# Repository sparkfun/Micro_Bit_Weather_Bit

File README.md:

SparkFun weather:bit - micro:bit Carrier Board (Qwiic)
========================================

[*SparkFun weather:bit (DEV-15837)*](https://www.sparkfun.com/products/15837)

The SparkFun weather:bit is a fully loaded “carrier” board for the micro:bit that, when combined with the micro:bit, provides you with a fully functional weather station. With the weather:bit you will have access to barometric pressure, relative humidity and temperature readings. There are also connections on this carrier board to optional sensors such as wind speed, direction, rain gauge and soil readings! The micro:bit has a lot of features and a lot of potential for weather data collection.

Repository Contents
-------------------

* **/Firmware** -  Example code used in the micro:climate Kit Experiment Guide. While they are compiled HEX codes, you can modify the example code once they are imported into MakeCode editor.
* **/Hardware** - Eagle design files (.brd, .sch)
* **/Production** - Production panel files (.brd)

Documentation
--------------
* **[Library](https://github.com/sparkfun/pxt-weather-bit)** - PXT weather:bit firmware
* **[micro:Climate Kit Experiment Guide](https://learn.sparkfun.com/tutorials/microclimate-kit-experiment-guide)** - Experiment guide using the weather:bit carrier board.
* **[Wireless Remote Weather Station with micro:bit](https://learn.sparkfun.com/tutorials/wireless-remote-weather-station-with-microbit/)** - Additional experiments for transmitting weather data wirelessly.

License Information
-------------------

This product is _**open source**_! 

Please review the LICENSE.md file for license information. 

If you have any questions or concerns on licensing, please contact technical support on our [SparkFun forums](https://forum.sparkfun.com/viewforum.php?f=152).

Distributed as-is; no warranty is given.

- Your friends at SparkFun.

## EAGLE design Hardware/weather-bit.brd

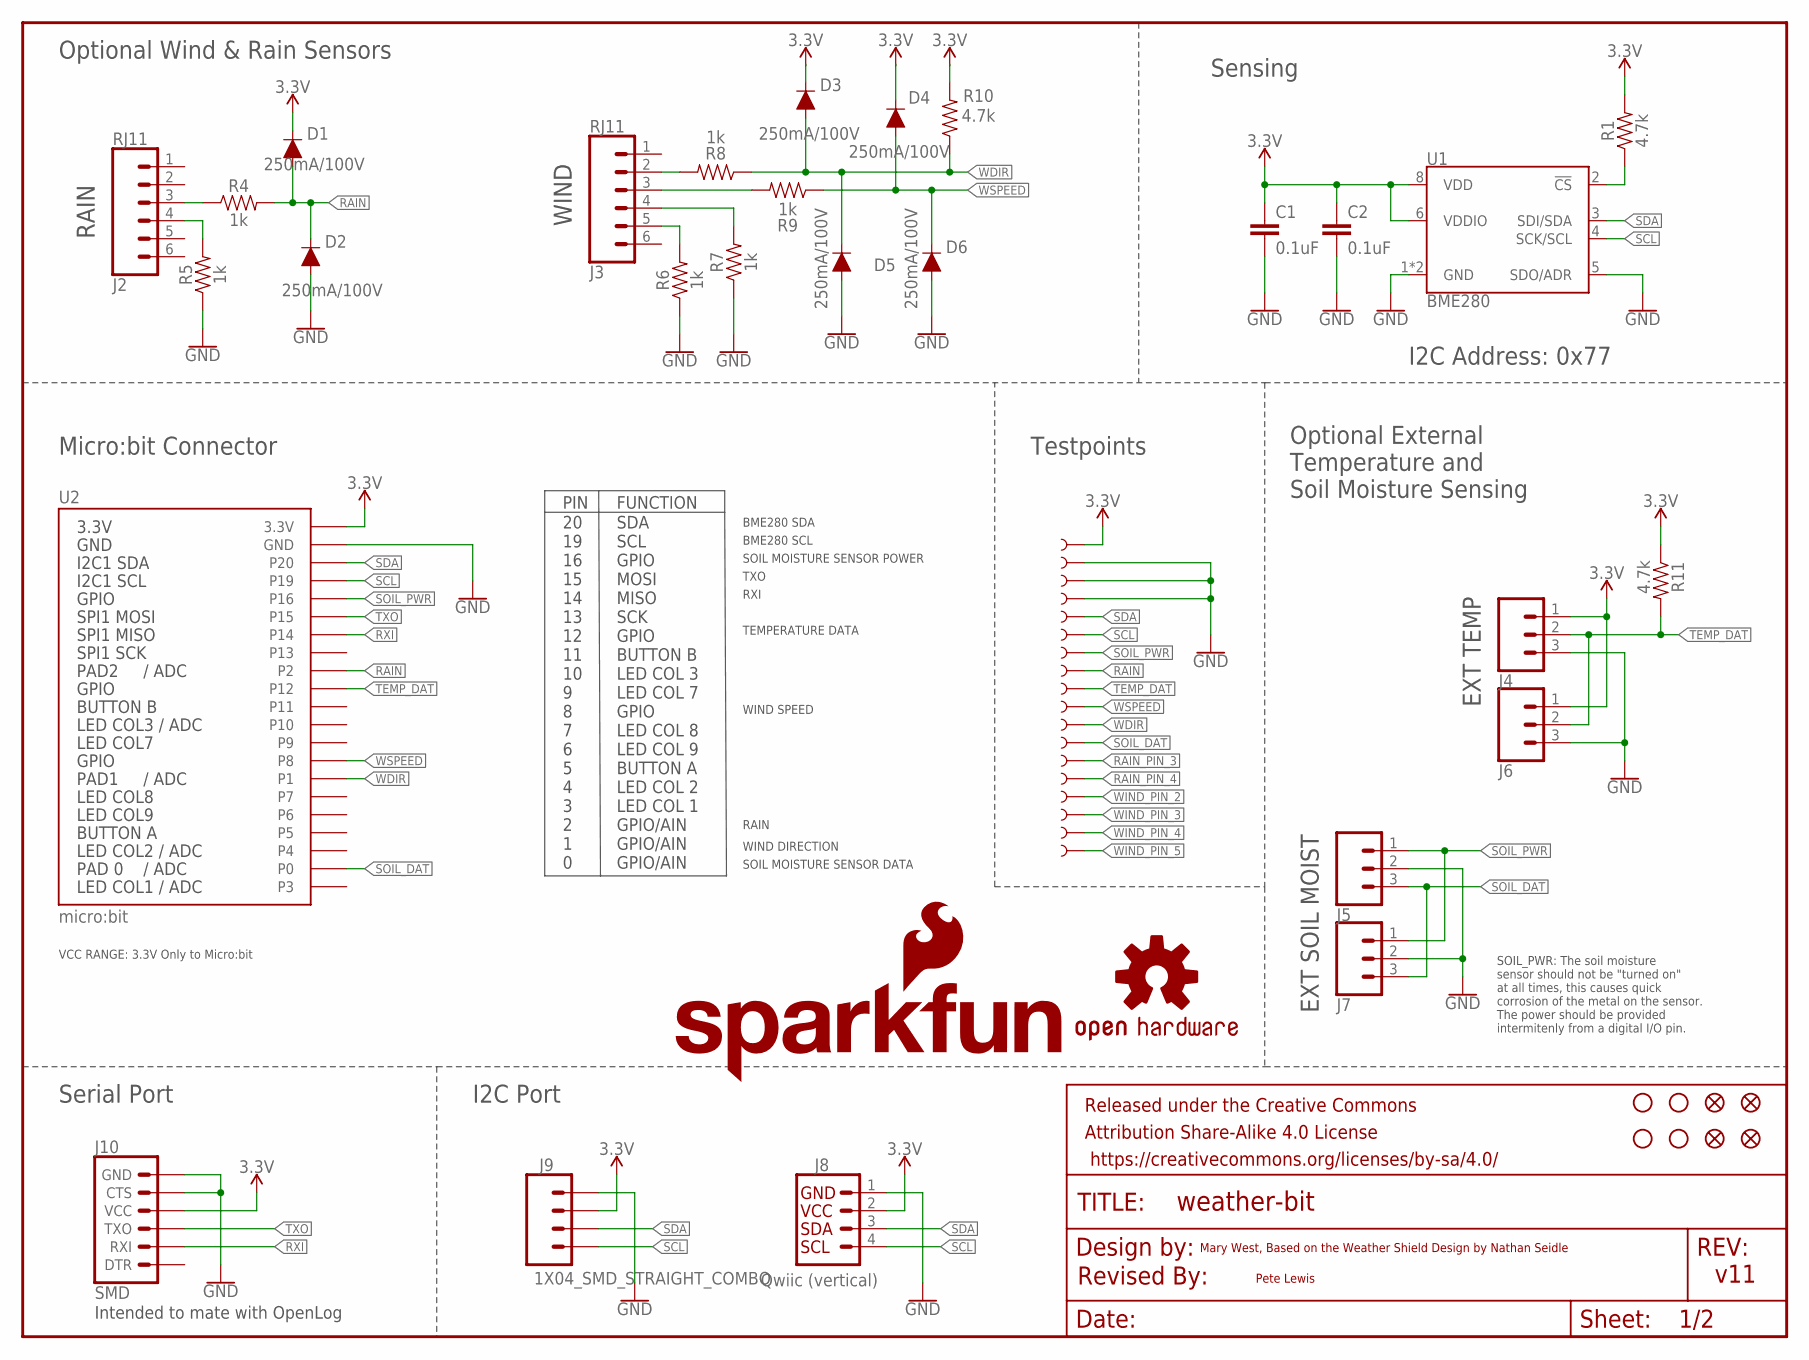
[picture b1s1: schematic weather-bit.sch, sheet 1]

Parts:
C1, C2: 0.1uF; 0603
D1, D2, D3, D4, D5, D6: 250mA/100V; SOD-323
FD1, FD2, FD3, FD4: FIDUCIAL1X2; FIDUCIAL-1X2
FRAME1: FRAME-LETTER; CREATIVE_COMMONS
H1, H2, H3, H4: STAND-OFF
J2, J3: RJ11; RJ11-6
J4, J5: CONN_03SCREW_LOCK; SCREWTERMINAL-3.5MM-3_LOCK.007S
J6, J7: CONN_03; 1X03
J8: Qwiic (vertical); JST04_1MM_VERT
J9: 1X04_SMD_STRAIGHT_COMBO; 1X04_SMD_VERTICAL_COMBO
J10: SMD; 6_PIN_SERIAL_TARGET_SIDE_VERT_SMT
LOGO2: SFE_LOGO_NAME_FLAME.3_INCH; SFE_LOGO_NAME_FLAME_.3
LOGO3: OSHW-LOGOL; OSHW-LOGO-L
R1, R10, R11: 4.7k; 0603
R4, R5, R6, R7, R8, R9: 1k; 0603
TP1, TP2, TP3, TP4, TP5, TP8, TP9, TP13, TP14, TP16, TP17, TP19: TEST-POINTTP_15TH_THRU; TP_15TH
TP6, TP7, TP10, TP11, TP12, TP15: TEST-POINT3X4; PAD.03X.04
U1: BME280; LGA-8-2.5X2.5
U2: micro:bit; MICRO:BIT-RA_SMD

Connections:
3.3V: C1.1, C2.1, D1.C, D3.C, D4.C, J4.1, J6.1, J8.2, J9.3, J9.3-2 (3), J10.4 (VCC), J10.4-2 (VCC), R1.2, R10.2, R11.1, TP1.P$1, U1.6 (VDDIO), U1.8 (VDD), U2.P$27 (3.3V), U2.P$28 (3.3V), U2.P$29 (3.3V), U2.P$30 (3.3V), U2.P$31 (3.3V), U2.P$32 (3.3V)
GND: C1.2, C2.2, D2.A, D5.A, D6.A, J4.3, J5.2, J6.3, J7.2, J8.1, J9.4, J9.4-2 (4), J10.5 (CTS), J10.5-2 (CTS), J10.6 (GND), J10.6-2 (GND), R5.1, R6.1, R7.1, TP2.P$1, TP16.P$1, TP17.P$1, U1.1 (GND), U1.5 (SDO/ADR), U1.7 (GND), U2.P$35 (GND), U2.P$36 (GND), U2.P$37 (GND), U2.P$38 (GND), U2.P$39 (GND), U2.P$40 (GND)
unnamed: R1.1, U1.2 (!CS)
RAIN: D1.A, D2.C, R4.2, TP8.P$1, U2.P$19 (P2), U2.P$20 (P2), U2.P$21 (P2), U2.P$22 (P2)
RAIN_PIN_3: J2.3, R4.1, TP6.P$1
RAIN_PIN_4: J2.4, R5.2, TP7.P$1
RXI: J10.3 (RXI), J10.3-2 (RXI), U2.P$24 (P14)
SCL: J8.4, J9.1, J9.1-2 (1), TP4.P$1, U1.4 (SCK/SCL), U2.P$33 (P19)
SDA: J8.3, J9.2, J9.2-2 (2), TP3.P$1, U1.3 (SDI/SDA), U2.P$34 (P20)
SOIL_DAT: J5.3, J7.3, TP19.P$1, U2.P$2 (P0), U2.P$3 (P0), U2.P$4 (P0), U2.P$5 (P0)
SOIL_PWR: J5.1, J7.1, TP5.P$1, U2.P$26 (P16)
TEMP_DAT: J4.2, J6.2, R11.2, TP9.P$1, U2.P$18 (P12), U2.P$23 (P13)
TXO: J10.2 (TXO), J10.2-2 (TXO), U2.P$25 (P15)
WDIR: D3.A, D5.C, R8.1, R10.1, TP14.P$1, U2.P$10 (P1), U2.P$11 (P1), U2.P$12 (P1), U2.P$13 (P1)
WIND_PIN_2: J3.2, R8.2, TP10.P$1
WIND_PIN_3: J3.3, R9.2, TP11.P$1
WIND_PIN_4: J3.4, R7.2, TP12.P$1
WIND_PIN_5: J3.5, R6.2, TP15.P$1
WSPEED: D4.A, D6.C, R9.1, TP13.P$1, U2.P$14 (P8)

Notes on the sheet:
v11
Micro:bit Connector
20 19 16 15 14 13 12 11 10 9 8 7 6 5 4 3 2 1 0
SDA SCL GPIO MOSI MISO SCK GPIO BUTTON B LED COL 3 LED COL 7 GPIO LED COL 8 LED COL 9 BUTTON A LED COL 2 LED COL 1 GPIO/AIN GPIO/AIN GPIO/AIN
PIN
FUNCTION
SOIL MOISTURE SENSOR DATA
BME280 SDA
BME280 SCL
SOIL MOISTURE SENSOR POWER
TEMPERATURE DATA
WIND DIRECTION
WIND SPEED
RAIN
TXO
RXI
Mary West, Based on the Weather Shield Design by Nathan Seidle
I2C Address: 0x77
Sensing
WIND
Optional Wind & Rain Sensors
Optional External Temperature and Soil Moisture Sensing
SOIL_PWR: The soil moisture sensor should not be "turned on" at all times, this causes quick corrosion of the metal on the sensor. The power should be provided intermitenly from a digital I/O pin.
EXT TEMP
EXT SOIL MOIST
Serial Port
I2C Port
Intended to mate with OpenLog
Pete Lewis
Revised By:
VCC RANGE: 3.3V Only to Micro:bit
Testpoints

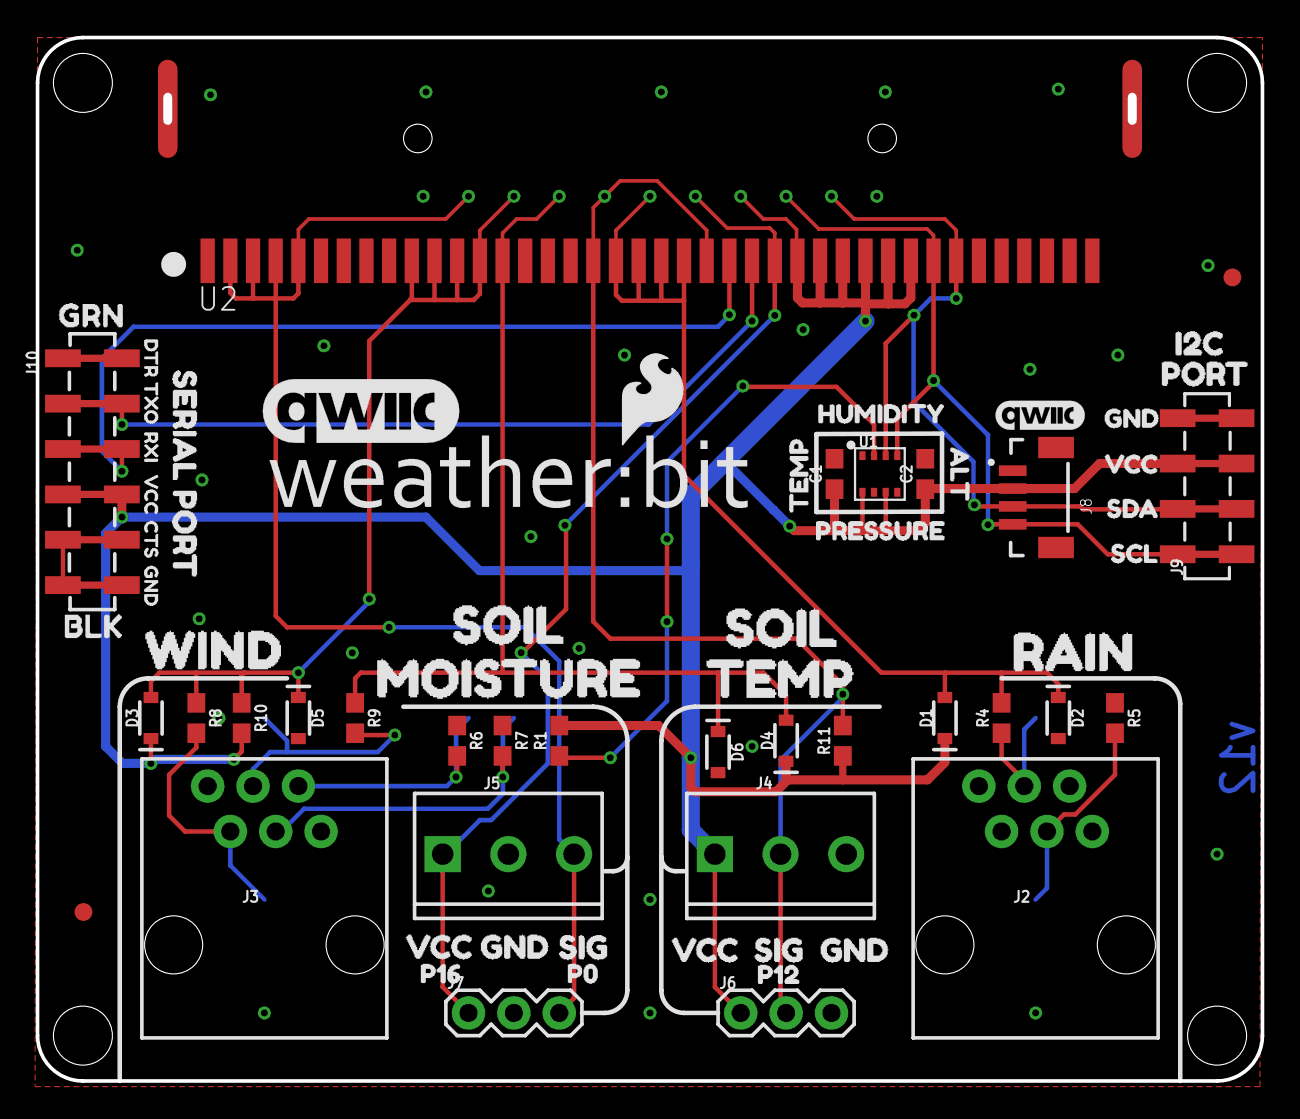
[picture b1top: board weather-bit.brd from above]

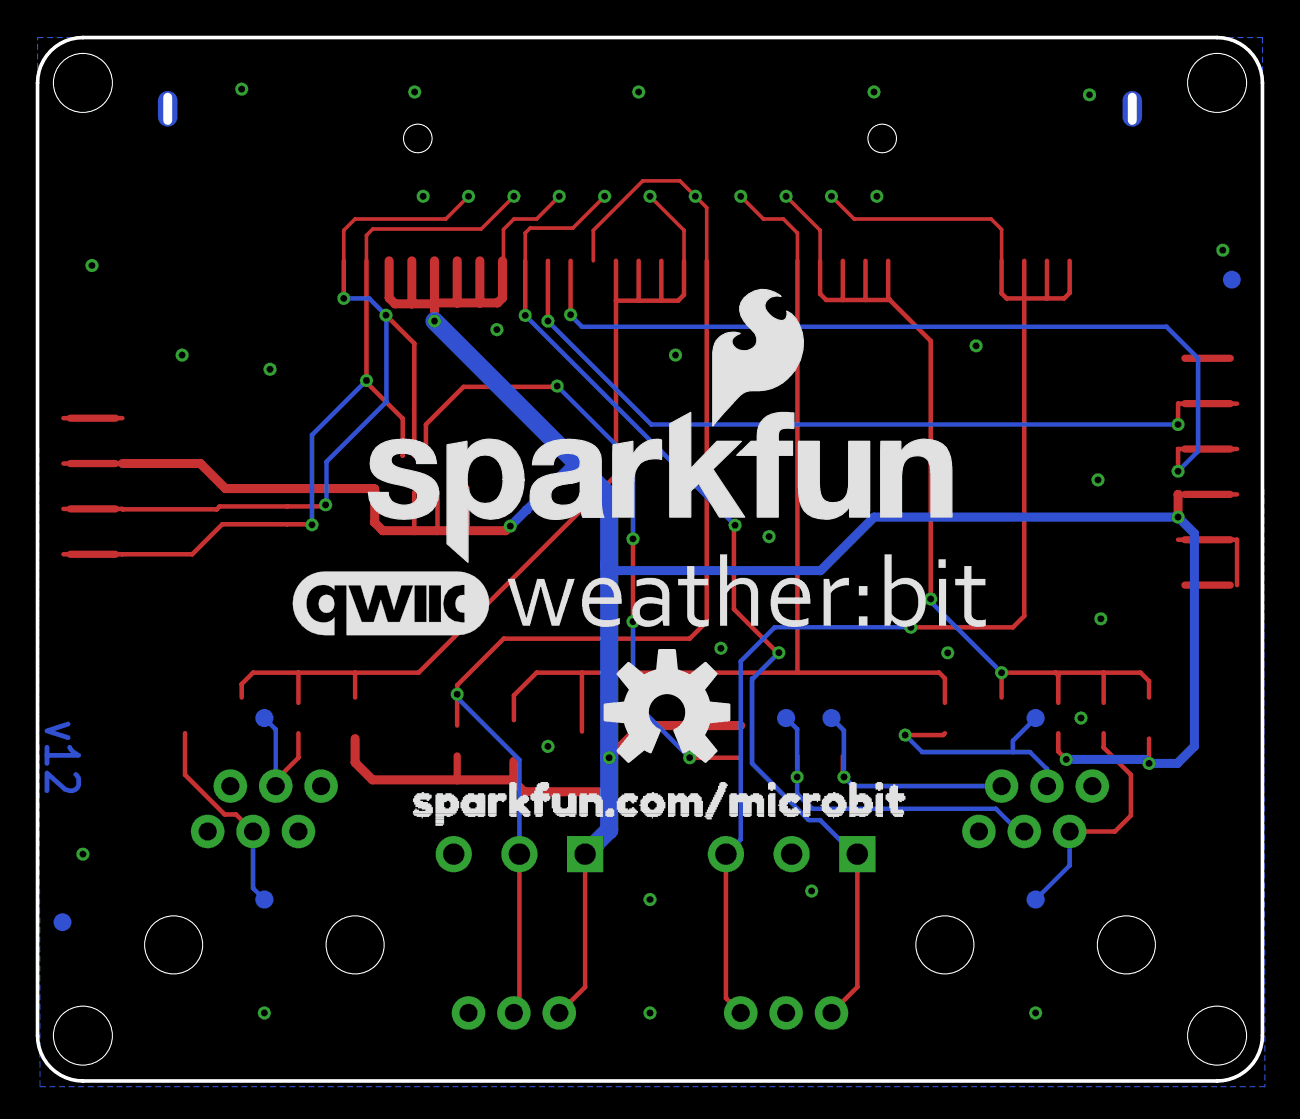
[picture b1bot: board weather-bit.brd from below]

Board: 2 copper layers, 68.3 x 58.1 mm, 91 parts (13 on the bottom side), 19 nets.

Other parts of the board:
U$1: SFE_LOGO_FLAME_.2
U$2, U$3: LOGO-WEATHERBIT
U$4: ORDERING_INSTRUCTIONS
U$5: QWIIC_5MM
U$6, U$7: QWIIC_11MM
U$8: I2C1
U$9: PORT2
U$10: SERIAL_PORT0
U$11: WIND12
U$12, U$13: SOIL13
U$14: MOISTURE14
U$15: TEMP15
U$16: RAIN16
U$17, U$21: VCC6
U$18, U$22: GND7
U$19, U$20: SIG8
U$23: P169
U$24: P010
U$25: P1211
U$26: HUMIDITY3
U$27: TEMP4
U$28: PRESSURE5
U$29: GND18
U$30: VCC19
U$31: SDA20
U$32: SCL21
U$33: SPARKFUN#COM#MICROBIT17
U$34: ALT0

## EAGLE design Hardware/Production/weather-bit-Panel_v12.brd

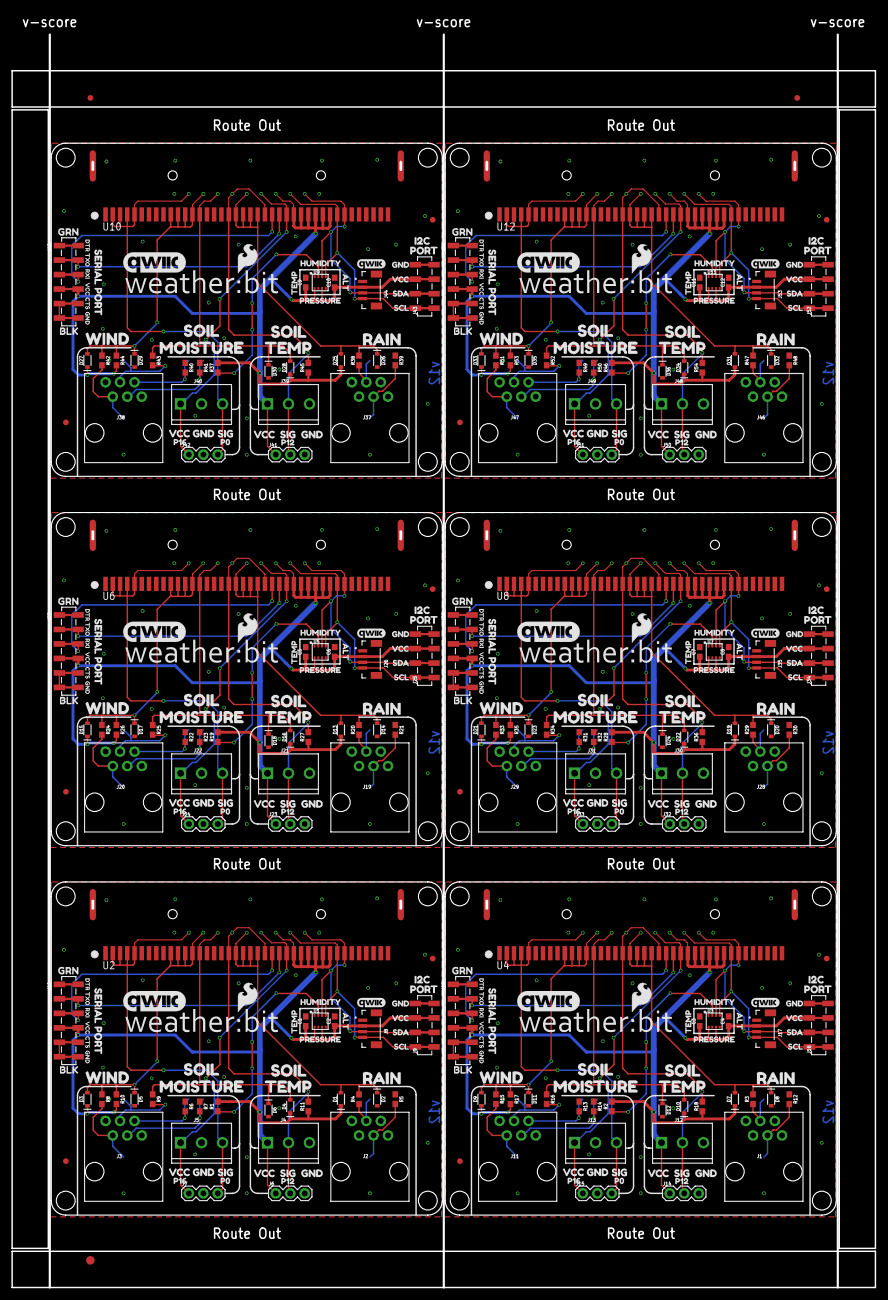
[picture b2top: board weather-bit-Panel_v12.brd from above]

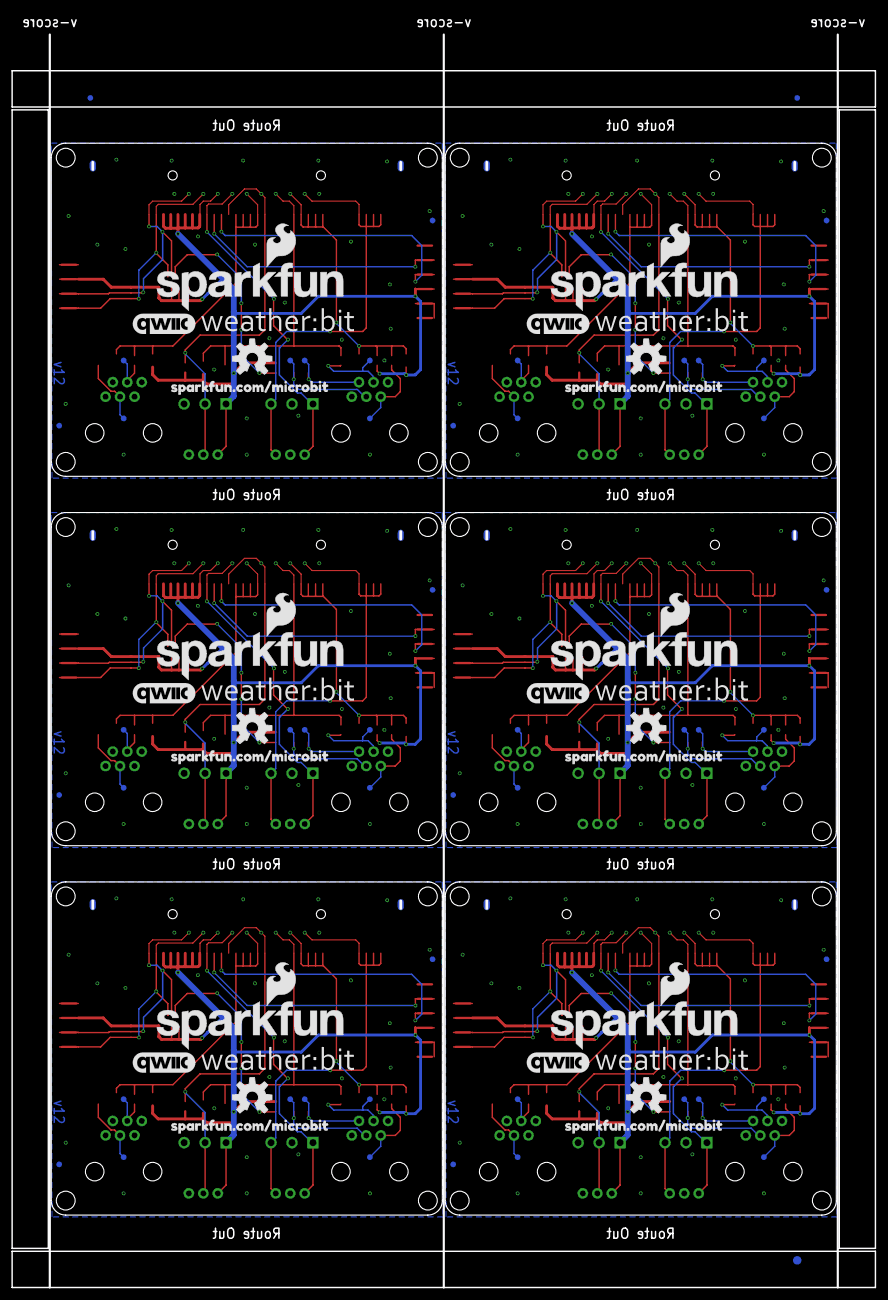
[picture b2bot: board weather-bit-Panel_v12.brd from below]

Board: 2 copper layers, 151.1 x 223.5 mm, 540 parts (81 on the bottom side), 114 nets.

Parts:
C1, C2, C3, C4, C5, C6, C7, C8, C9, C10, C11, C12: 0.1uF; 0603
D1, D2, D3, D4, D5, D6, D7, D8, D9, D10, D11, D12, D13, D14, D15, D16, D17, D18, D19, D20, D21, D22, D23, D24, D25, D26, D27, D28, D29, D30, D31, D32, D33, D34, D35, D36: 250mA/100V; SOD-323
E$1, E$2, E$3, E$4: FIDUCIAL-1X2
E$5, E$6: FIDUCIAL-1.5X3
FD1, FD2, FD3, FD4, FD5, FD6, FD7, FD8, FD9, FD10, FD11, FD12, FD13, FD14, FD15, FD16, FD17, FD18, FD19, FD20, FD21, FD22, FD23, FD24: FIDUCIAL1X2; FIDUCIAL-1X2
H1, H2, H3, H4, H5, H6, H7, H8, H9, H10, H11, H12, H13, H14, H15, H16, H17, H18, H19, H20, H21, H22, H23, H24: STAND-OFF
J1, J2, J3, J11, J19, J20, J28, J29, J37, J38, J46, J47: RJ11; RJ11-6
J4, J5, J12, J13, J21, J22, J30, J31, J39, J40, J48, J49: SCREWTERMINAL-3.5MM-3_LOCK.007S
J6, J7, J14, J15, J23, J24, J32, J33, J41, J42, J50, J51: 1X03
J8, J17, J26, J35, J44, J53: Qwiic (vertical); JST04_1MM_VERT
J9, J16, J25, J34, J43, J52: 1X04_SMD_STRAIGHT_COMBO; 1X04_SMD_VERTICAL_COMBO
J10, J18, J27, J36, J45, J54: SMD; 6_PIN_SERIAL_TARGET_SIDE_VERT_SMT
LOGO1, LOGO3, LOGO5, LOGO7, LOGO9, LOGO11: OSHW-LOGOL; OSHW-LOGO-L
LOGO2, LOGO4, LOGO6, LOGO8, LOGO10, LOGO12: SFE_LOGO_NAME_FLAME.3_INCH; SFE_LOGO_NAME_FLAME_.3
R1, R2, R10, R11, R17, R18, R19, R26, R27, R28, R35, R36, R37, R44, R45, R46, R53, R54: 4.7k; 0603
R3, R4, R5, R6, R7, R8, R9, R12, R13, R14, R15, R16, R20, R21, R22, R23, R24, R25, R29, R30, R31, R32, R33, R34, R38, R39, R40, R41, R42, R43, R47, R48, R49, R50, R51, R52: 1k; 0603
TP1, TP2, TP3, TP4, TP5, TP8, TP9, TP13, TP14, TP16, TP17, TP18, TP19, TP20, TP21, TP22, TP23, TP24, TP25, TP26, TP27, TP28, TP35, TP36, TP37, TP38, TP39, TP40, TP41, TP42, TP43, TP44, TP45, TP46, TP53, TP54, TP55, TP56, TP57, TP58, TP59, TP60, TP61, TP62, TP63, TP64, TP71, TP72, TP73, TP74, TP75, TP76, TP77, TP78, TP79, TP80, TP81, TP82, TP89, TP90, TP91, TP92, TP93, TP94, TP95, TP96, TP97, TP98, TP99, TP100, TP107, TP108: TP_15TH
TP6, TP7, TP10, TP11, TP12, TP15, TP29, TP30, TP31, TP32, TP33, TP34, TP47, TP48, TP49, TP50, TP51, TP52, TP65, TP66, TP67, TP68, TP69, TP70, TP83, TP84, TP85, TP86, TP87, TP88, TP101, TP102, TP103, TP104, TP105, TP106: PAD.03X.04
U1, U3, U5, U7, U9, U11: BME280; LGA-8-2.5X2.5
U2, U4, U6, U8, U10, U12: micro:bit; MICRO:BIT-RA_SMD
U$1, U$4, U$67, U$100, U$133, U$166: SFE_LOGO_FLAME_.2
U$2, U$3, U$35, U$36, U$68, U$69, U$101, U$102, U$134, U$135, U$167, U$168: LOGO-WEATHERBIT
U$5, U$37, U$70, U$103, U$136, U$169: QWIIC_5MM
U$6, U$7, U$38, U$39, U$71, U$72, U$104, U$105, U$137, U$138, U$170, U$171: QWIIC_11MM
U$8, U$40, U$73, U$106, U$139, U$172: I2C1
U$9, U$41, U$74, U$107, U$140, U$173: PORT2
U$10, U$42, U$75, U$108, U$141, U$174: SERIAL_PORT0
U$11, U$43, U$76, U$109, U$142, U$175: WIND12
U$12, U$13, U$44, U$45, U$77, U$78, U$110, U$111, U$143, U$144, U$176, U$177: SOIL13
U$14, U$46, U$79, U$112, U$145, U$178: MOISTURE14
U$15, U$47, U$80, U$113, U$146, U$179: TEMP15
U$16, U$48, U$81, U$114, U$147, U$180: RAIN16
U$17, U$21, U$49, U$53, U$82, U$86, U$115, U$119, U$148, U$152, U$181, U$185: VCC6
U$18, U$22, U$50, U$54, U$83, U$87, U$116, U$120, U$149, U$153, U$182, U$186: GND7
U$19, U$20, U$51, U$52, U$84, U$85, U$117, U$118, U$150, U$151, U$183, U$184: SIG8
U$23, U$55, U$88, U$121, U$154, U$187: P169
U$24, U$56, U$89, U$122, U$155, U$188: P010
U$25, U$57, U$90, U$123, U$156, U$189: P1211
U$26, U$58, U$91, U$124, U$157, U$190: HUMIDITY3
U$27, U$59, U$92, U$125, U$158, U$191: TEMP4
U$28, U$60, U$93, U$126, U$159, U$192: PRESSURE5
U$29, U$61, U$94, U$127, U$160, U$193: GND18
U$30, U$62, U$95, U$128, U$161, U$194: VCC19
U$31, U$63, U$96, U$129, U$162, U$195: SDA20
U$32, U$64, U$97, U$130, U$163, U$196: SCL21
U$33, U$65, U$98, U$131, U$164, U$197: SPARKFUN#COM#MICROBIT17
U$34, U$66, U$99, U$132, U$165, U$198: ALT0

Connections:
3.3V: C1.1, C2.1, D1.C, D3.C, D4.C, J4.1, J6.1, J8.2, J9.3, J9.3-2, J10.4, J10.4-2, R1.2, R10.2, R11.1, TP1.P$1, U1.6, U1.8, U2.P$27, U2.P$28, U2.P$29, U2.P$30, U2.P$31, U2.P$32
3.3V1: C3.1, C4.1, D7.C, D9.C, D10.C, J12.1, J14.1, J16.3, J16.3-2, J17.2, J18.4, J18.4-2, R2.2, R17.2, R18.1, TP18.P$1, U3.6, U3.8, U4.P$27, U4.P$28, U4.P$29, U4.P$30, U4.P$31, U4.P$32
3.3V2: C5.1, C6.1, D13.C, D15.C, D16.C, J21.1, J23.1, J25.3, J25.3-2, J26.2, J27.4, J27.4-2, R19.2, R26.2, R27.1, TP37.P$1, U5.6, U5.8, U6.P$27, U6.P$28, U6.P$29, U6.P$30, U6.P$31, U6.P$32
3.3V3: C7.1, C8.1, D19.C, D21.C, D22.C, J30.1, J32.1, J34.3, J34.3-2, J35.2, J36.4, J36.4-2, R28.2, R35.2, R36.1, TP55.P$1, U7.6, U7.8, U8.P$27, U8.P$28, U8.P$29, U8.P$30, U8.P$31, U8.P$32
3.3V4: C9.1, C10.1, D25.C, D27.C, D28.C, J39.1, J41.1, J43.3, J43.3-2, J44.2, J45.4, J45.4-2, R37.2, R44.2, R45.1, TP73.P$1, U9.6, U9.8, U10.P$27, U10.P$28, U10.P$29, U10.P$30, U10.P$31, U10.P$32
3.3V5: C11.1, C12.1, D31.C, D33.C, D34.C, J48.1, J50.1, J52.3, J52.3-2, J53.2, J54.4, J54.4-2, R46.2, R53.2, R54.1, TP91.P$1, U11.6, U11.8, U12.P$27, U12.P$28, U12.P$29, U12.P$30, U12.P$31, U12.P$32
GND: C1.2, C2.2, D2.A, D5.A, D6.A, J4.3, J5.2, J6.3, J7.2, J8.1, J9.4, J9.4-2, J10.5, J10.5-2, J10.6, J10.6-2, R5.1, R6.1, R7.1, TP2.P$1, TP16.P$1, TP17.P$1, U1.1, U1.5, U1.7, U2.P$35, U2.P$36, U2.P$37, U2.P$38, U2.P$39, U2.P$40
GND1: C3.2, C4.2, D8.A, D11.A, D12.A, J12.3, J13.2, J14.3, J15.2, J16.4, J16.4-2, J17.1, J18.5, J18.5-2, J18.6, J18.6-2, R12.1, R13.1, R14.1, TP20.P$1, TP35.P$1, TP36.P$1, U3.1, U3.5, U3.7, U4.P$35, U4.P$36, U4.P$37, U4.P$38, U4.P$39, U4.P$40
GND2: C5.2, C6.2, D14.A, D17.A, D18.A, J21.3, J22.2, J23.3, J24.2, J25.4, J25.4-2, J26.1, J27.5, J27.5-2, J27.6, J27.6-2, R21.1, R22.1, R23.1, TP38.P$1, TP53.P$1, TP54.P$1, U5.1, U5.5, U5.7, U6.P$35, U6.P$36, U6.P$37, U6.P$38, U6.P$39, U6.P$40
GND3: C7.2, C8.2, D20.A, D23.A, D24.A, J30.3, J31.2, J32.3, J33.2, J34.4, J34.4-2, J35.1, J36.5, J36.5-2, J36.6, J36.6-2, R30.1, R31.1, R32.1, TP56.P$1, TP71.P$1, TP72.P$1, U7.1, U7.5, U7.7, U8.P$35, U8.P$36, U8.P$37, U8.P$38, U8.P$39, U8.P$40
GND4: C9.2, C10.2, D26.A, D29.A, D30.A, J39.3, J40.2, J41.3, J42.2, J43.4, J43.4-2, J44.1, J45.5, J45.5-2, J45.6, J45.6-2, R39.1, R40.1, R41.1, TP74.P$1, TP89.P$1, TP90.P$1, U9.1, U9.5, U9.7, U10.P$35, U10.P$36, U10.P$37, U10.P$38, U10.P$39, U10.P$40
GND5: C11.2, C12.2, D32.A, D35.A, D36.A, J48.3, J49.2, J50.3, J51.2, J52.4, J52.4-2, J53.1, J54.5, J54.5-2, J54.6, J54.6-2, R48.1, R49.1, R50.1, TP92.P$1, TP107.P$1, TP108.P$1, U11.1, U11.5, U11.7, U12.P$35, U12.P$36, U12.P$37, U12.P$38, U12.P$39, U12.P$40
unnamed: R2.1, U3.2
unnamed: R1.1, U1.2
unnamed: R19.1, U5.2
unnamed: R28.1, U7.2
unnamed: R37.1, U9.2
unnamed: R46.1, U11.2
RAIN: D1.A, D2.C, R4.2, TP8.P$1, U2.P$19, U2.P$20, U2.P$21, U2.P$22
RAIN1: D7.A, D8.C, R3.2, TP24.P$1, U4.P$19, U4.P$20, U4.P$21, U4.P$22
RAIN2: D13.A, D14.C, R20.2, TP42.P$1, U6.P$19, U6.P$20, U6.P$21, U6.P$22
RAIN3: D19.A, D20.C, R29.2, TP60.P$1, U8.P$19, U8.P$20, U8.P$21, U8.P$22
RAIN4: D25.A, D26.C, R38.2, TP78.P$1, U10.P$19, U10.P$20, U10.P$21, U10.P$22
RAIN5: D31.A, D32.C, R47.2, TP96.P$1, U12.P$19, U12.P$20, U12.P$21, U12.P$22
RAIN_PIN_1: J1.3, R3.1, TP29.P$1
RAIN_PIN_2: J1.4, R12.2, TP30.P$1
RAIN_PIN_3: J2.3, R4.1, TP6.P$1
RAIN_PIN_4: J2.4, R5.2, TP7.P$1
RAIN_PIN_5: J19.3, R20.1, TP47.P$1
RAIN_PIN_6: J19.4, R21.2, TP48.P$1
RAIN_PIN_7: J28.3, R29.1, TP65.P$1
RAIN_PIN_8: J28.4, R30.2, TP66.P$1
RAIN_PIN_9: J37.3, R38.1, TP83.P$1
RAIN_PIN_10: J37.4, R39.2, TP84.P$1
RAIN_PIN_11: J46.3, R47.1, TP101.P$1
RAIN_PIN_12: J46.4, R48.2, TP102.P$1
RXI: J10.3, J10.3-2, U2.P$24
RXI1: J18.3, J18.3-2, U4.P$24
RXI2: J27.3, J27.3-2, U6.P$24
RXI3: J36.3, J36.3-2, U8.P$24
RXI4: J45.3, J45.3-2, U10.P$24
RXI5: J54.3, J54.3-2, U12.P$24
SCL: J8.4, J9.1, J9.1-2, TP4.P$1, U1.4, U2.P$33
SCL1: J16.1, J16.1-2, J17.4, TP22.P$1, U3.4, U4.P$33
SCL2: J25.1, J25.1-2, J26.4, TP40.P$1, U5.4, U6.P$33
SCL3: J34.1, J34.1-2, J35.4, TP58.P$1, U7.4, U8.P$33
SCL4: J43.1, J43.1-2, J44.4, TP76.P$1, U9.4, U10.P$33
SCL5: J52.1, J52.1-2, J53.4, TP94.P$1, U11.4, U12.P$33
SDA: J8.3, J9.2, J9.2-2, TP3.P$1, U1.3, U2.P$34
SDA1: J16.2, J16.2-2, J17.3, TP21.P$1, U3.3, U4.P$34
SDA2: J25.2, J25.2-2, J26.3, TP39.P$1, U5.3, U6.P$34
SDA3: J34.2, J34.2-2, J35.3, TP57.P$1, U7.3, U8.P$34
SDA4: J43.2, J43.2-2, J44.3, TP75.P$1, U9.3, U10.P$34
SDA5: J52.2, J52.2-2, J53.3, TP93.P$1, U11.3, U12.P$34
SOIL_DAT: J5.3, J7.3, TP19.P$1, U2.P$2, U2.P$3, U2.P$4, U2.P$5
SOIL_DAT1: J13.3, J15.3, TP28.P$1, U4.P$2, U4.P$3, U4.P$4, U4.P$5
SOIL_DAT2: J22.3, J24.3, TP46.P$1, U6.P$2, U6.P$3, U6.P$4, U6.P$5
SOIL_DAT3: J31.3, J33.3, TP64.P$1, U8.P$2, U8.P$3, U8.P$4, U8.P$5
SOIL_DAT4: J40.3, J42.3, TP82.P$1, U10.P$2, U10.P$3, U10.P$4, U10.P$5
SOIL_DAT5: J49.3, J51.3, TP100.P$1, U12.P$2, U12.P$3, U12.P$4, U12.P$5
SOIL_PWR: J5.1, J7.1, TP5.P$1, U2.P$26
SOIL_PWR1: J13.1, J15.1, TP23.P$1, U4.P$26
SOIL_PWR2: J22.1, J24.1, TP41.P$1, U6.P$26
SOIL_PWR3: J31.1, J33.1, TP59.P$1, U8.P$26
SOIL_PWR4: J40.1, J42.1, TP77.P$1, U10.P$26
SOIL_PWR5: J49.1, J51.1, TP95.P$1, U12.P$26
TEMP_DAT: J4.2, J6.2, R11.2, TP9.P$1, U2.P$18, U2.P$23
TEMP_DAT1: J12.2, J14.2, R18.2, TP25.P$1, U4.P$18, U4.P$23
TEMP_DAT2: J21.2, J23.2, R27.2, TP43.P$1, U6.P$18, U6.P$23
TEMP_DAT3: J30.2, J32.2, R36.2, TP61.P$1, U8.P$18, U8.P$23
TEMP_DAT4: J39.2, J41.2, R45.2, TP79.P$1, U10.P$18, U10.P$23
TEMP_DAT5: J48.2, J50.2, R54.2, TP97.P$1, U12.P$18, U12.P$23
TXO: J10.2, J10.2-2, U2.P$25
TXO1: J18.2, J18.2-2, U4.P$25
TXO2: J27.2, J27.2-2, U6.P$25
TXO3: J36.2, J36.2-2, U8.P$25
TXO4: J45.2, J45.2-2, U10.P$25
TXO5: J54.2, J54.2-2, U12.P$25
WDIR: D3.A, D5.C, R8.1, R10.1, TP14.P$1, U2.P$10, U2.P$11, U2.P$12, U2.P$13
WDIR1: D9.A, D11.C, R15.1, R17.1, TP27.P$1, U4.P$10, U4.P$11, U4.P$12, U4.P$13
WDIR2: D15.A, D17.C, R24.1, R26.1, TP45.P$1, U6.P$10, U6.P$11, U6.P$12, U6.P$13
WDIR3: D21.A, D23.C, R33.1, R35.1, TP63.P$1, U8.P$10, U8.P$11, U8.P$12, U8.P$13
WDIR4: D27.A, D29.C, R42.1, R44.1, TP81.P$1, U10.P$10, U10.P$11, U10.P$12, U10.P$13
WDIR5: D33.A, D35.C, R51.1, R53.1, TP99.P$1, U12.P$10, U12.P$11, U12.P$12, U12.P$13
WIND_PIN_1: J11.3, R16.2, TP32.P$1
WIND_PIN_2: J3.2, R8.2, TP10.P$1
WIND_PIN_3: J3.3, R9.2, TP11.P$1
WIND_PIN_4: J3.4, R7.2, TP12.P$1
WIND_PIN_5: J3.5, R6.2, TP15.P$1
WIND_PIN_6: J11.5, R13.2, TP34.P$1
WIND_PIN_7: J11.4, R14.2, TP33.P$1
WIND_PIN_8: J11.2, R15.2, TP31.P$1
WIND_PIN_9: J20.3, R25.2, TP50.P$1
WIND_PIN_10: J20.5, R22.2, TP52.P$1
WIND_PIN_11: J20.4, R23.2, TP51.P$1
WIND_PIN_12: J20.2, R24.2, TP49.P$1
WIND_PIN_13: J29.3, R34.2, TP68.P$1
WIND_PIN_14: J29.5, R31.2, TP70.P$1
WIND_PIN_15: J29.4, R32.2, TP69.P$1
WIND_PIN_16: J29.2, R33.2, TP67.P$1
WIND_PIN_17: J38.3, R43.2, TP86.P$1
WIND_PIN_18: J38.5, R40.2, TP88.P$1
WIND_PIN_19: J38.4, R41.2, TP87.P$1
WIND_PIN_20: J38.2, R42.2, TP85.P$1
WIND_PIN_21: J47.3, R52.2, TP104.P$1
WIND_PIN_22: J47.5, R49.2, TP106.P$1
WIND_PIN_23: J47.4, R50.2, TP105.P$1
WIND_PIN_24: J47.2, R51.2, TP103.P$1
WSPEED: D4.A, D6.C, R9.1, TP13.P$1, U2.P$14
WSPEED1: D10.A, D12.C, R16.1, TP26.P$1, U4.P$14
WSPEED2: D16.A, D18.C, R25.1, TP44.P$1, U6.P$14
WSPEED3: D22.A, D24.C, R34.1, TP62.P$1, U8.P$14
WSPEED4: D28.A, D30.C, R43.1, TP80.P$1, U10.P$14
WSPEED5: D34.A, D36.C, R52.1, TP98.P$1, U12.P$14

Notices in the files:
parts and their libraries:
SparkFun-Aesthetics: Licensing: Creative Commons ShareAlike 4.0 International - https://creativecommons.org/licenses/by-sa/4.0
SparkFun-Aesthetics: Released under the Creative Commons Attribution Share-Alike 4.0 License
SparkFun-Aesthetics: https://creativecommons.org/licenses/by-sa/4.0
